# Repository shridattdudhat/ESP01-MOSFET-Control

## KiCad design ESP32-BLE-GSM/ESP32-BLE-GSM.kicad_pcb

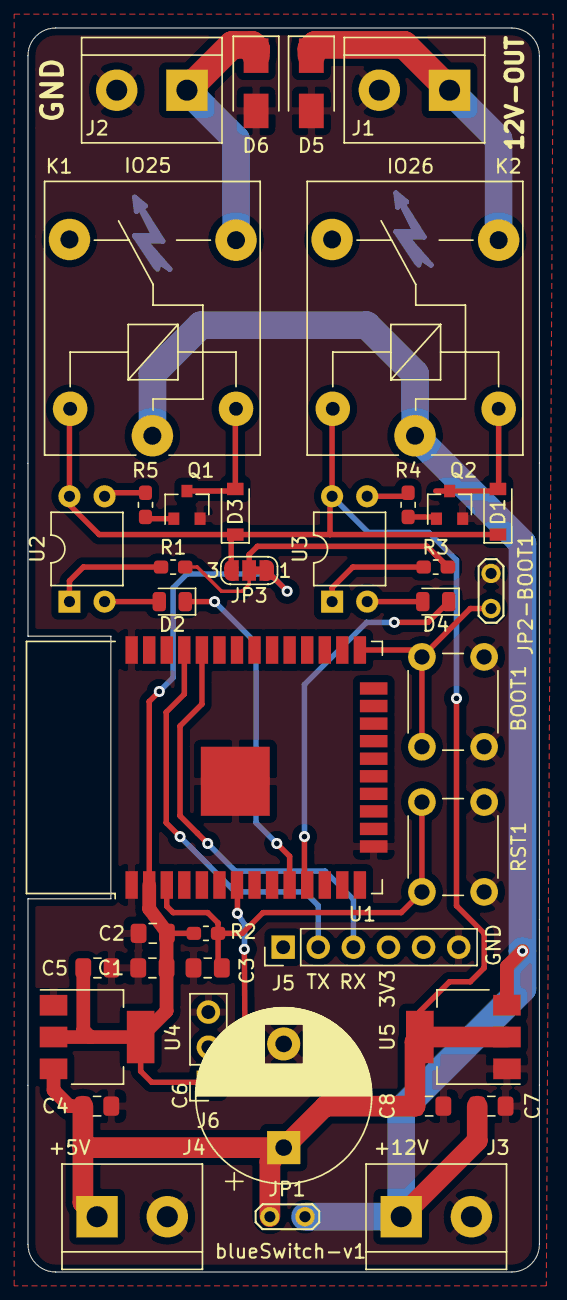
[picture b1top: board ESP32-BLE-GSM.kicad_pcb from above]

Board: 2 copper layers, 37.0 x 90.0 mm, 39 parts (0 on the bottom side), 24 nets.

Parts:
BOOT1: SW_Push; SW_PUSH_6mm
C1, C2, C3: 0.1uF; C_0805_2012Metric_Pad1.15x1.40mm_HandSolder
C4, C5, C7, C8: 1uF; C_0805_2012Metric_Pad1.15x1.40mm_HandSolder
C6: CP1; CP_Radial_D12.5mm_P7.50mm
D1, D3: 1N4148W; D_SOD-123
D2, D4: LED; LED_0805_2012Metric
D5, D6: US1M; D_SMA
J1, J2, J3, J4: Screw_Terminal_01x02; TerminalBlock_bornier-2_P5.08mm
J5: Conn_01x06_Female; PinHeader_1x06_P2.54mm_Vertical
J6: Conn_01x03_Male; PinSocket_1x03_P2.54mm_Vertical
JP1, JP2-BOOT1: Jumper; TestPoint_2Pads_Pitch2.54mm_Drill0.8mm
JP3: Jumper_NC_Dual; SolderJumper-3_P1.3mm_Bridged12_RoundedPad1.0x1.5mm_NumberL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
K1, K2: SANYOU_SRD_Form_C; Relay_SPDT_SANYOU_SRD_Series_Form_C
Q1, Q2: BC817; SOT-23
R1, R3: 1K; R_0603_1608Metric_Pad1.05x0.95mm_HandSolder
R2: 10K; R_0603_1608Metric_Pad1.05x0.95mm_HandSolder
R4, R5: 500; R_0603_1608Metric_Pad1.05x0.95mm_HandSolder
RST1: SW_Push; SW_PUSH_6mm
U1: ESP32-WROOM-32
U2, U3: EL817; DIP-4_W7.62mm
U4: LM1117-3.3; SOT-223-3_TabPin2
U5: LM1117-5.0; SOT-223-3_TabPin2

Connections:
+3V3: C1.1, C2.1, C5.1, J6.1, JP3.1, R2.2, U1.2, U4.2
+5V: C4.1, C6.1, C8.1, D1.1, D3.1, J4.1, JP1.2, JP3.3, K1.5, K2.5, U2.4, U3.4, U4.3, U5.2
+12V: C7.1, J3.1, JP1.1, K1.1, K2.1, U5.3
/EN: C3.1, R2.1, RST1.1, U1.3
/IO0: BOOT1.1, JP2-BOOT1.1, U1.25
ADC1_7: J6.2, U1.7
GND: BOOT1.2, C1.2, C2.2, C3.2, C4.2, C5.2, C6.2, C7.2, C8.2, D5.2, D6.2, J1.2, J2.2, J3.2, J4.2, J5.6, J6.3, JP2-BOOT1.2, Q1.2, Q2.2, RST1.2, U1.1, U1.15, U1.38, U1.39, U4.1, U5.1
IO25: D2.1, U1.10
IO26: D4.1, U1.11
unnamed: D1.2, K2.2, Q2.3
unnamed: D2.2, U2.2
unnamed: D3.2, K1.2, Q1.3
unnamed: D4.2, U3.2
unnamed: D5.1, J1.1, K2.3
unnamed: D6.1, J2.1, K1.3
unnamed: Q1.1, R5.1
unnamed: Q2.1, R4.1
unnamed: R1.1, U2.1
unnamed: R3.1, U3.1
unnamed: R4.2, U3.3
unnamed: R5.2, U2.3
OPTO_VCC: JP3.2, R1.2, R3.2
RX0: J5.3, U1.34
TX0: J5.2, U1.35

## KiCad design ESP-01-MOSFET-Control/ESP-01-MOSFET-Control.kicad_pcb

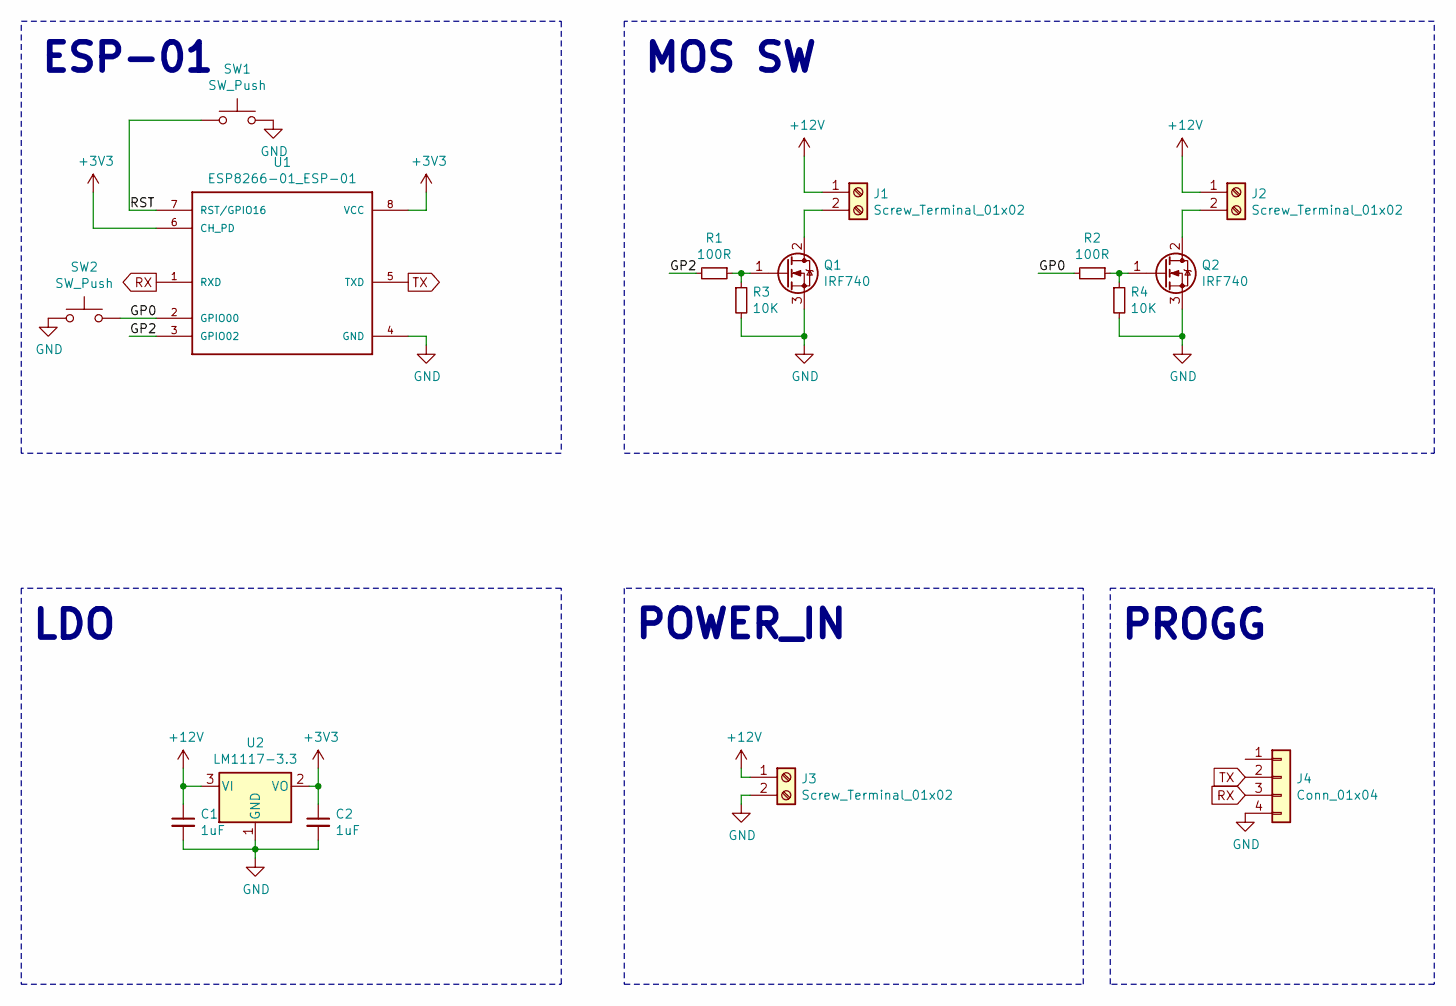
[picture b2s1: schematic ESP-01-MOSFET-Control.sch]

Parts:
C1, C2: 1uF; C_0805_2012Metric_Pad1.15x1.40mm_HandSolder
J1, J2, J3: Screw_Terminal_01x02; TerminalBlock_bornier-2_P5.08mm
J4: Conn_01x04; PinSocket_1x04_P2.54mm_Vertical
Q1, Q2: IRF740; TO-220-3_Vertical
R1, R2: 100R; R_0805_2012Metric_Pad1.15x1.40mm_HandSolder
R3, R4: 10K; R_0805_2012Metric_Pad1.15x1.40mm_HandSolder
SW1, SW2: SW_Push; SW_PUSH_6mm
U1: ESP8266-01_ESP-01; ESP-01
U2: LM1117-3.3; SOT-223-3_TabPin2

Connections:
+3V3: C2.1, U1.6 (CH_PD), U1.8 (VCC), U2.2 (VO)
+12V: C1.1, J1.1, J2.1, J3.1, U2.3 (VI)
/GP0: R2.2, SW2.2, U1.2 (GPIO00)
/GP2: R1.2, U1.3 (GPIO02)
/RST: SW1.1, U1.7 (RST/GPIO16)
GND: C1.2, C2.2, J3.2, J4.4, Q1.3 (S), Q2.3 (S), R3.2, R4.2, SW1.2, SW2.1, U1.4 (GND), U2.1 (GND)
unnamed: J1.2, Q1.2 (D)
unnamed: J2.2, Q2.2 (D)
unnamed: Q1.1 (G), R1.1, R3.1
unnamed: Q2.1 (G), R2.1, R4.1
RX: J4.3, U1.1 (RXD)
TX: J4.2, U1.5 (TXD)

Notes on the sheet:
ESP-01
MOS SW
LDO
POWER_IN
PROGG

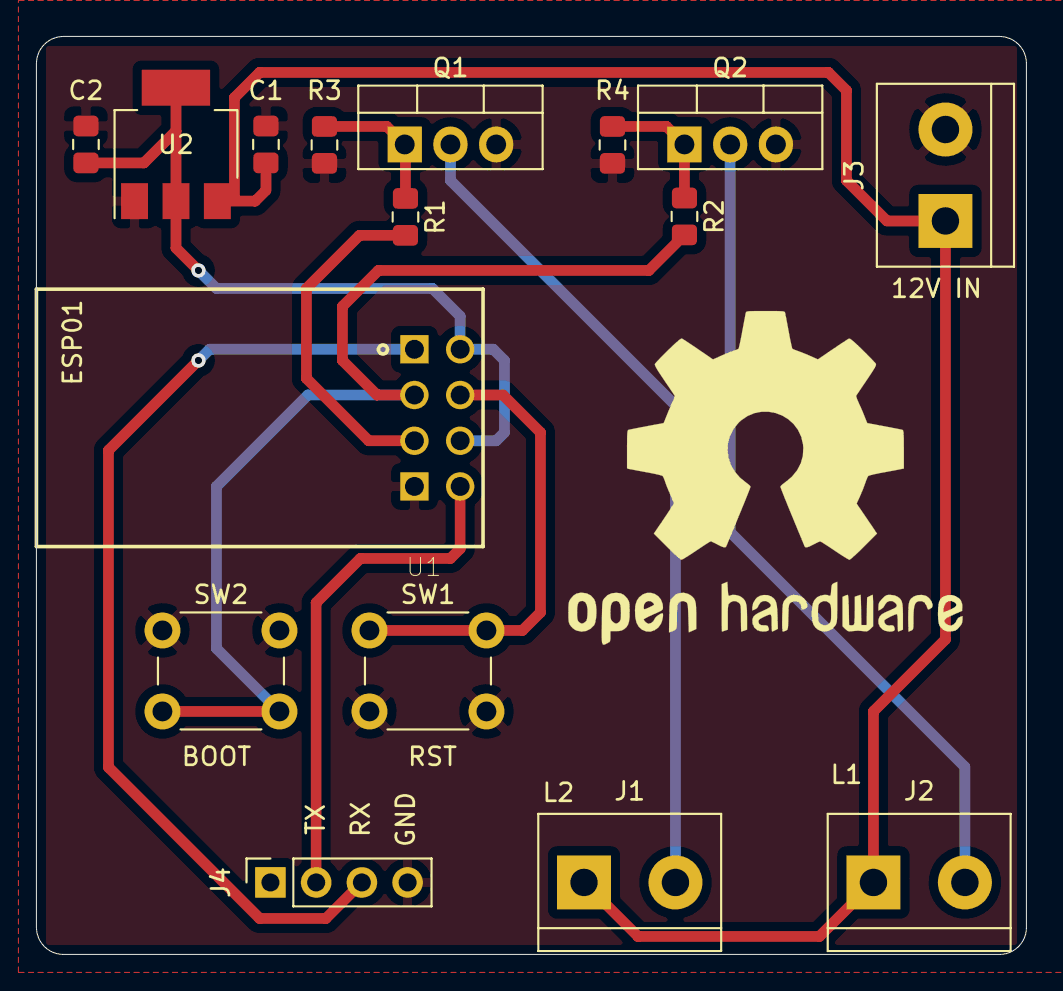
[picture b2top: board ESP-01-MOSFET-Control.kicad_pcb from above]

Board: 2 copper layers, 55.0 x 51.0 mm, 16 parts (0 on the bottom side), 12 nets.

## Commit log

2020-08-03 KiCAD Project
